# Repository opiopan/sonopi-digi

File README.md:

Sonopi Digi
===

Sonopi Digi is a hat card for Raspberry Pi to add a S/PDIF digital sound output capability.<br>
This hardware design is published under open source lincence. You can use and modify this design freely. There is also no limitation in commercial use.

In order to export digital sound signal, [Cirrus Logic WM8804](https://www.cirrus.com/products/wm8804/) is installed on Sonopi Digi as a S/PDIF transmitter.
There are many kind of Raspberry Pi Hats installed WM8804 in the world. This IC is a defacto standard to add a S/PDIF output functionality to Raspberry Pi.

## Design Goals
1. **Target to casual use and reasonable cost**<br>
Sonopy Digi is not a device for audiophiles. It's a just simple solution to realize connectivity to audio amplifier without serious noise. I don't expect to install expensive parts and also don't expect to stick to beautiful circuit patterning to improve analog characteristics.<br>
Sonopi Digi should be realized with minimum components, and should be eliminated analog circuit portion. Therefore, only optical output is installed on this product. An coaxial output which need analog driver circuit is not suitable to Sonopi Digi design policy.

2. **Not necessory any additional software**<br>
I don't want to make any software to use Sonopy Digi. Sonopi Digi should be designed to work by using standard device driver and standard device tree overlay configuration.<br>
Specifically, Sonopi Digi is designed to work when following line is added to `/boot/config.txt`.

    ```
    dtoverlay=hifiberry-digi
    ```

## Design Overview
The keypoint of Sonopi Digi hardware design is configuring WM8804 to adapt to following device driver and device tree configuration.

- [hifiberry-digi-overlay.dts](https://github.com/raspberrypi/linux/blob/e2d2941326922b63d722ebc46520c3a2287b675f/arch/arm/boot/dts/overlays/hifiberry-digi-overlay.dts)
- [rpi-wm8804-soundcard.c](https://github.com/raspberrypi/linux/blob/e2d2941326922b63d722ebc46520c3a2287b675f/sound/soc/bcm/rpi-wm8804-soundcard.c)

These files shows following condition regarding WM8804 configuration.

- Must be driven 27MHz crystal oscillation circuit
- Must be configureed with 2 wire software mode.
- I2C device address must be 0x3b

That means WM8804 pin condition should be as below.

WM8804 PIN        |   Configuration
------------------|-------------------------------------------------
XIN(11), XOP(10)  | 27MHz crystal
RSTB(6)           | Pull up to 3.3V
SDIN(3)           | Raspberry Pi I2C1 SDA pin
GPO0(2)           | Pull down to GND
CSB(5)            | Pull up to 3.3V
SCLK(1)           | Raspberry Pi I2C1 SCL
BCLK(14)          | Raspberry Pi I2S BCLK
LRCLK(15)         | Raspberry Pi I2S LRCLK
DIN(13)           | Raspberry Pi I2S DOUT
TXO(17)           | Optical S/PDIF transmitter module

## PoC Result
The PoC is concluded with great success.

## PCB Design

- **Gerber Data**<br>
Eagle PCB design files are placed at [here](./pcb/). You can also use [this gerber file archive](https://raw.githubusercontent.com/wiki/opiopan/sonopi-digi/data/sonopi-digi-gerber-1.1.zip) to order PCB production.

- **BOM**<br>
    
    Components | Value / Product Number | Remarks
    -----------|------------------------|------------------------------
    IC1        | Cirrus Logic WM8804    |
    X1         | 27MHz Crystal (3225)   | load capacitance: 15pF
    R1         | BCN164AB103J7          | resistor array 10K ohm x 4
    C1, C5     | 1uF (1608)             |
    C2         | 0.1uF (1608)           |
    C3, C4     | 27pF (1608)            | need to change value if X1's load capacitance is not 15pF
    J1         | PLT133/T10W            | optical S/PDIF transmitter

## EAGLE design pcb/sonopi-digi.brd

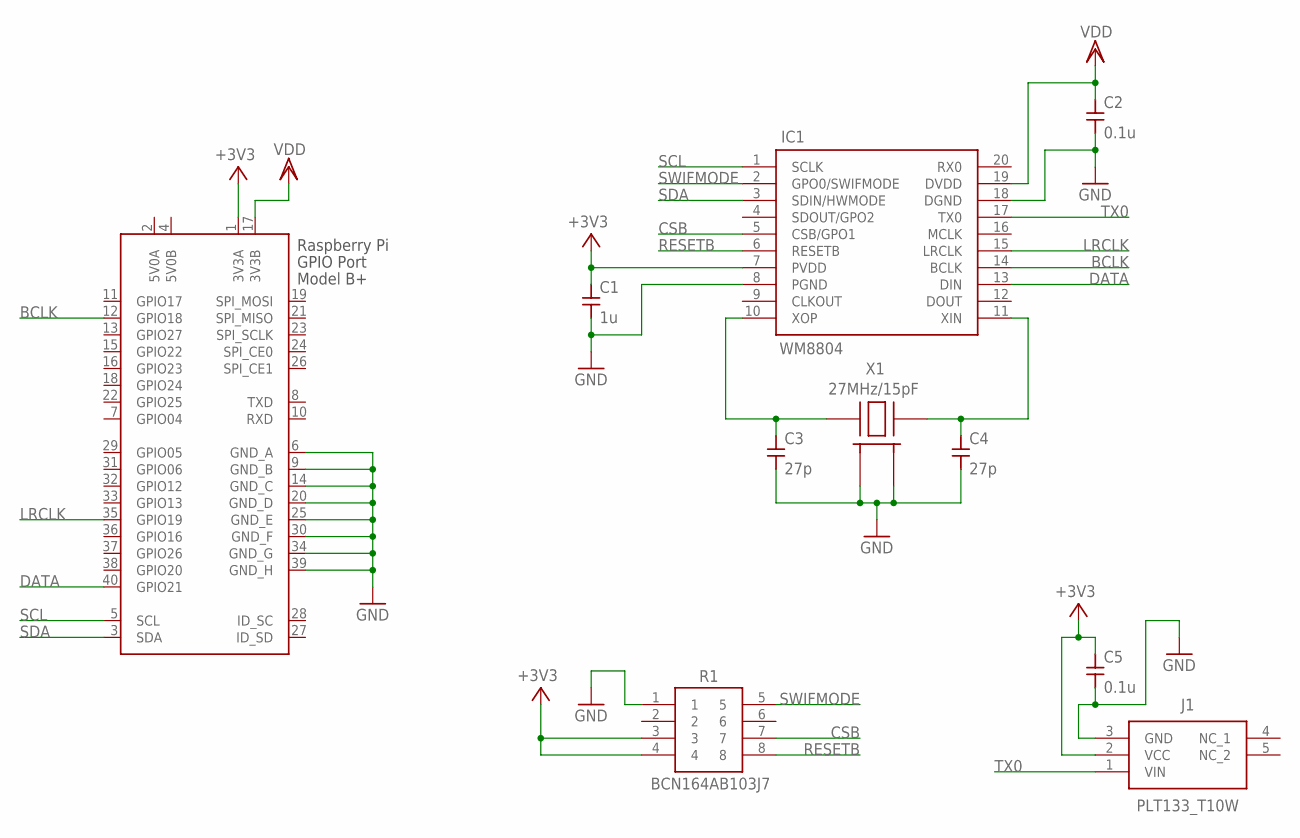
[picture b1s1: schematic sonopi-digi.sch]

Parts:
C1: 1u; SMD1608
C2, C5: 0.1u; SMD1608
C3, C4: 27p; SMD1608
IC1: WM8804; SOP65P780X200-20N
J1: PLT133_T10W; PLT133T10W
J2: RASPI_BOARD_B+#_SMALL; RASPI_BOARD_B+HAT_SMALL
R1: BCN164AB103J7; BCN164A_1
X1: 27MHz/15pF; CRYSTAL3225-HS

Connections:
5V0A: J2.2 (5V0A)
5V0B: J2.4 (5V0B)
+3V3: C1.1, C5.1, IC1.7 (PVDD), J1.2 (VCC), J2.1 (3V3A), R1.3, R1.4
BCLK: IC1.14 (BCLK), J2.12 (GPIO18)
CSB: IC1.5 (CSB/GPO1), R1.7
DATA: IC1.13 (DIN), J2.40 (GPIO21)
GND: C1.2, C2.2, C3.2, C4.2, C5.2, IC1.8 (PGND), IC1.18 (DGND), J1.3 (GND), J2.6 (GND_A), J2.9 (GND_B), J2.14 (GND_C), J2.20 (GND_D), J2.25 (GND_E), J2.30 (GND_F), J2.34 (GND_G), J2.39 (GND_H), R1.1, X1.2 (GND_1), X1.4 (GND_2)
LRCLK: IC1.15 (LRCLK), J2.35 (GPIO19)
RESETB: IC1.6 (RESETB), R1.8
SCL: IC1.1 (SCLK), J2.5 (SCL)
SDA: IC1.3 (SDIN/HWMODE), J2.3 (SDA)
SWIFMODE: IC1.2 (GPO0/SWIFMODE), R1.5
TX0: IC1.17 (TX0), J1.1 (VIN)
VDD: C2.1, IC1.19 (DVDD), J2.17 (3V3B)
XIN: C4.1, IC1.11 (XIN), X1.3 (HOT_2)
XOP: C3.1, IC1.10 (XOP), X1.1 (HOT_1)

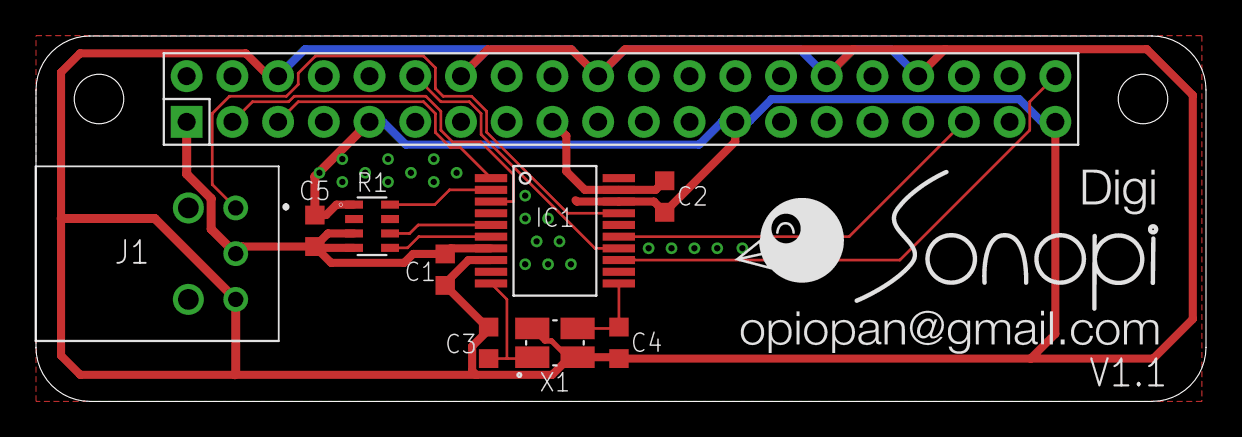
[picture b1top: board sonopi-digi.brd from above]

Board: 2 copper layers, 65.0 x 20.3 mm, 11 parts (0 on the bottom side), 14 nets.

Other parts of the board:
U$1: SONOPI-DIGI-LOGO

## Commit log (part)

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2019-02-26 PoC has been done
2019-02-26 Create LICENSE
2019-03-01 add pcb design
2019-03-03 complete PCB design
2019-03-03 add gerbview project file
2019-03-04 improve wiring
2019-03-31 add panelizing script
2019-03-31 fix a minor issue
2019-04-10 update project status
2019-04-23 fix a S/PDIF transmitter pin assign issue
